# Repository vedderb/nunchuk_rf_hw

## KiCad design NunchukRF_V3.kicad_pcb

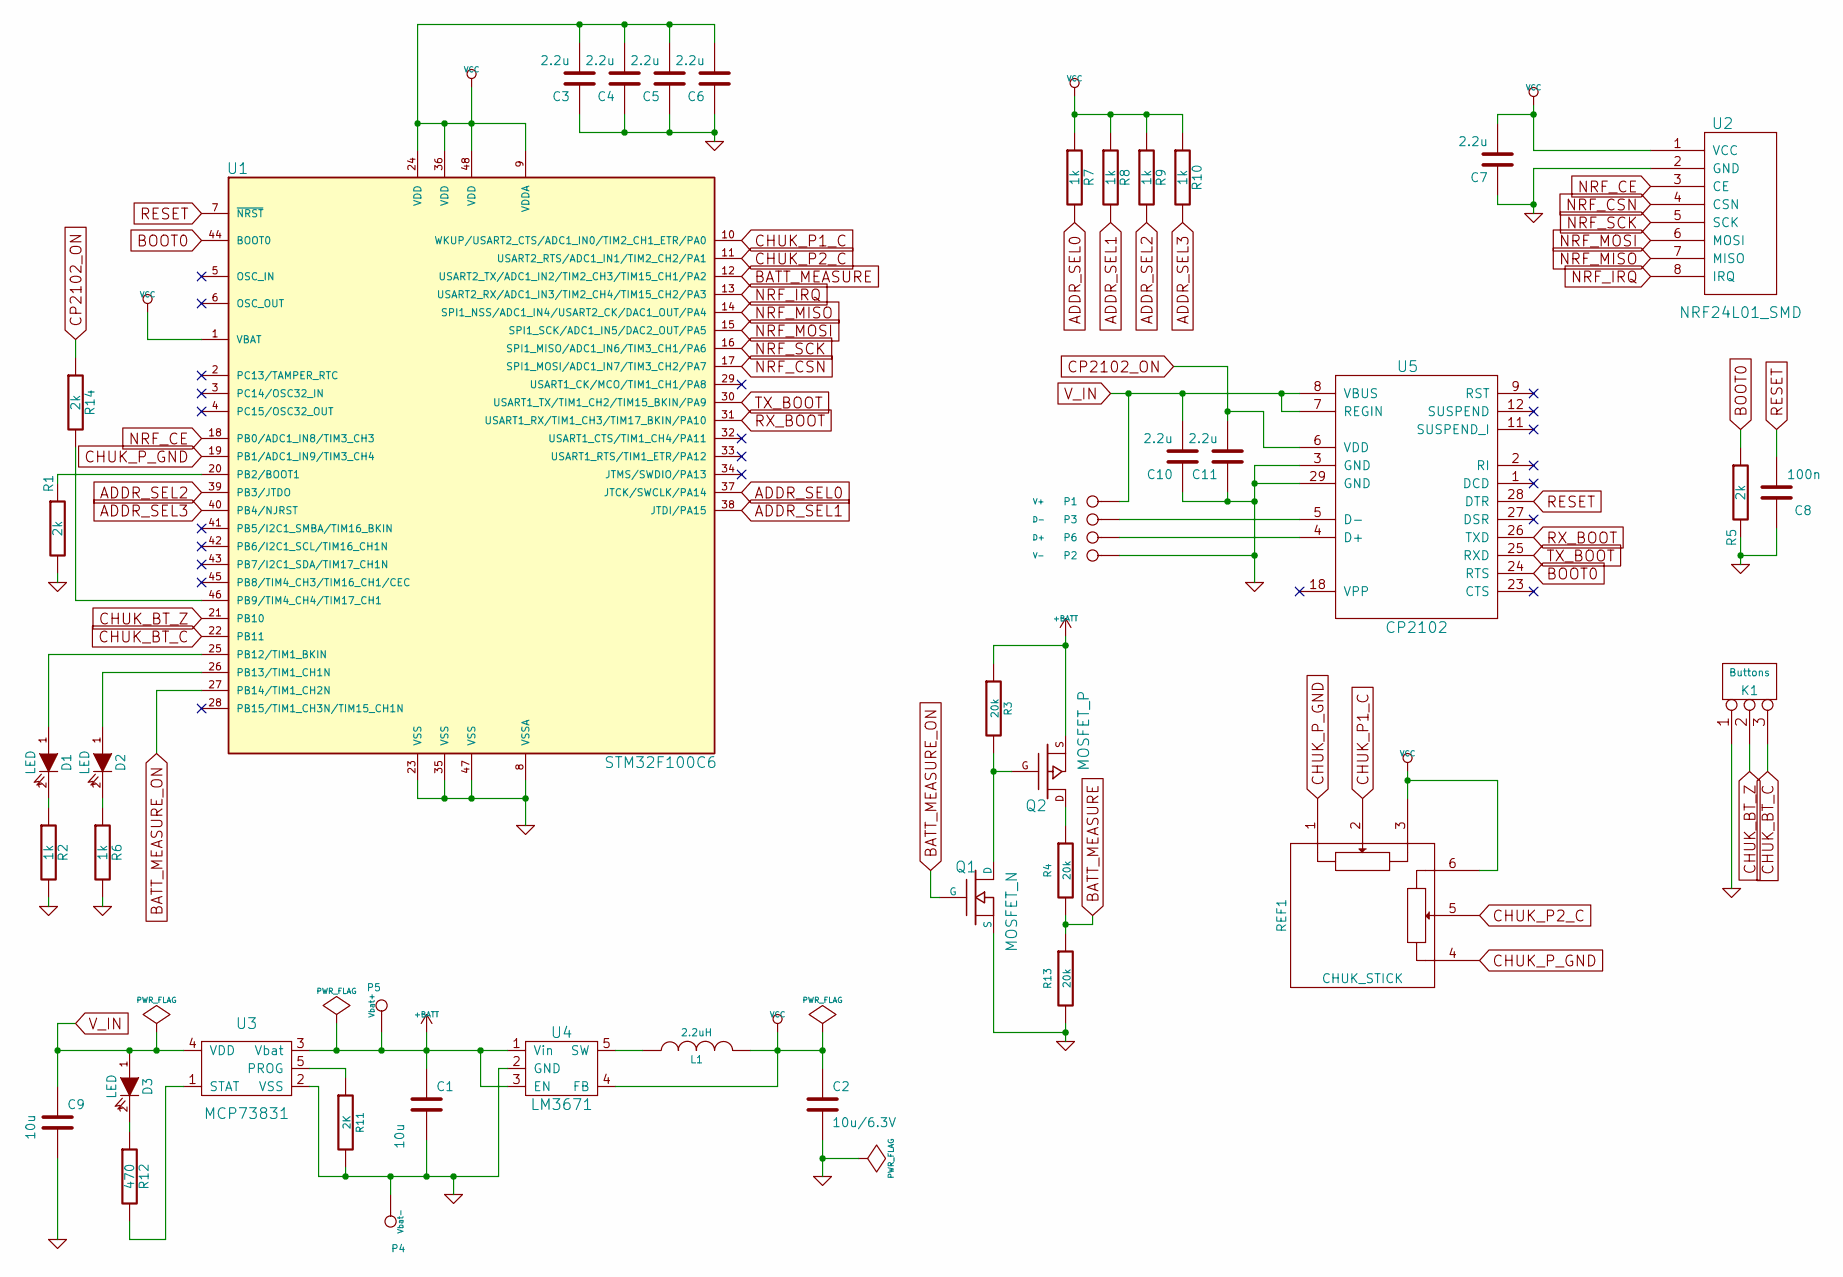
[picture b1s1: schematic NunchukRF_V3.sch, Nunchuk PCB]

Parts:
C1, C9: 10u; C_0603_HandSoldering
C2: 10u/6.3V; C_0603_HandSoldering
C3, C4, C5, C6, C7, C10, C11: 2.2u; C_0603_HandSoldering
C8: 100n; C_0603_HandSoldering
D1, D2, D3: LED; LED-0805
K1: Buttons; Wafer_Vertical10x5.8x7RM2.5-3
L1: 2.2uH; R_0805_HandSoldering
P1: V+; 1PAD_Small
P2: V-; 1PAD_Small
P3: D-; 1PAD_Small
P4: Vbat-; 1PAD_Small
P5: Vbat+; 1PAD_Small
P6: D+; 1PAD_Small
Q1: MOSFET_N; SOT23GDS
Q2: MOSFET_P; SOT23GDS
R1, R5, R14: 2k; R_0603_HandSoldering
R2, R6, R7, R8, R9, R10: 1k; R_0603_HandSoldering
R3, R4, R13: 20k; R_0603_HandSoldering
R11: 2K; R_0603_HandSoldering
R12: 470; R_0603_HandSoldering
REF1: CHUK_STICK; chuk_stick_2
U1: STM32F100C6; lqfp48_pad_mod
U2: NRF24L01_SMD
U3: MCP73831; SOT23-5
U4: LM3671; SOT23-5
U5: CP2102; qfn-28

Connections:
+BATT: C1.1, P5.1, Q2.S, R3.1, U3.3 (Vbat), U4.1 (Vin), U4.3 (EN)
ADDR_SEL0: R7.2, U1.37 (JTCK/SWCLK/PA14)
ADDR_SEL1: R8.2, U1.38 (JTDI/PA15)
ADDR_SEL2: R9.2, U1.39 (PB3/JTDO)
ADDR_SEL3: R10.2, U1.40 (PB4/NJRST)
BATT_MEASURE: R4.2, R13.1, U1.12 (USART2_TX/ADC1_IN2/TIM2_CH3/TIM15_CH1/P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)
BATT_MEASURE_ON: Q1.G, U1.27 (PB14/TIM1_CH2N)
BOOT0: R5.1, U1.44 (BOOT0), U5.24 (RTS)
CHUK_BT_C: K1.3, U1.22 (PB11)
CHUK_BT_Z: K1.2 (PM), U1.21 (PB10)
CHUK_P1_C: REF1.2 (P1_B), U1.10 (WKUP/USART2_CTS/ADC1_IN0/TIM2_CH1_ETR/P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)
CHUK_P2_C: REF1.5 (P2_B), U1.11 (USART2_RTS/ADC1_IN1/TIM2_CH2/PA1)
CHUK_P_GND: REF1.1 (P1_A), REF1.4 (P2_A), U1.19 (PB1/ADC1_IN9/TIM3_CH4)
CP2102_ON: C11.2, R14.1, U5.6 (VDD)
GND: C1.2, C2.2, C3.1, C4.1, C5.1, C6.1, C7.1, C8.1, C9.2, C10.1, C11.1, K1.1, P2.1, P4.1, Q1.S, R1.2, R2.2, R5.2, R6.2, R11.2, R13.2, U1.8 (VSSA), U1.23 (VSS), U1.35 (VSS), U1.47 (VSS), U2.2 (GND), U3.2 (VSS), U4.2 (GND), U5.3 (GND), U5.29 (GND)
NRF_CE: U1.18 (PB0/ADC1_IN8/TIM3_CH3), U2.3 (CE)
NRF_CSN: U1.17 (SPI1_MOSI/ADC1_IN7/TIM3_CH2/PA7), U2.4 (CSN)
NRF_IRQ: U1.13 (USART2_RX/ADC1_IN3/TIM2_CH4/TIM15_CH2/P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), U2.8 (IRQ)
NRF_MISO: U1.14 (SPI1_NSS/ADC1_IN4/USART2_CK/DAC1_OUT/PA4), U2.7 (MISO)
NRF_MOSI: U1.15 (SPI1_SCK/ADC1_IN5/DAC2_OUT/PA5), U2.6 (MOSI)
NRF_SCK: U1.16 (SPI1_MISO/ADC1_IN6/TIM3_CH1/PA6), U2.5 (SCK)
unnamed: D1.1 (A), U1.25 (PB12/TIM1_BKIN)
unnamed: D1.2 (K), R2.1
unnamed: D2.1 (A), U1.26 (PB13/TIM1_CH1N)
unnamed: D2.2 (K), R6.1
unnamed: D3.2 (K), R12.1
unnamed: L1.1, U4.5 (SW)
unnamed: P3.1, U5.5 (D-)
unnamed: P6.1, U5.4 (D+)
unnamed: Q1.D, Q2.G, R3.2
unnamed: Q2.D, R4.1
unnamed: R1.1, U1.20 (PB2/BOOT1)
unnamed: R11.1, U3.5 (PROG)
unnamed: R12.2, U3.1 (STAT)
unnamed: R14.2, U1.46 (PB9/TIM4_CH4/TIM17_CH1)
RESET: C8.2, U1.7 (~NRST), U5.28 (DTR)
RX_BOOT: U1.31 (USART1_RX/TIM1_CH3/TIM17_BKIN/PA10), U5.26 (TXD)
TX_BOOT: U1.30 (USART1_TX/TIM1_CH2/TIM15_BKIN/PA9), U5.25 (RXD)
VCC: C2.1, C3.2, C4.2, C5.2, C6.2, C7.2, L1.2, R7.1, R8.1, R9.1, R10.1, REF1.3 (P1_C), REF1.6 (P2_C), U1.1 (VBAT), U1.9 (VDDA), U1.24 (VDD), U1.36 (VDD), U1.48 (VDD), U2.1 (VCC), U4.4 (FB)
V_IN: C9.1, C10.2, D3.1 (A), P1.1, U3.4 (VDD), U5.7 (REGIN), U5.8 (VBUS)

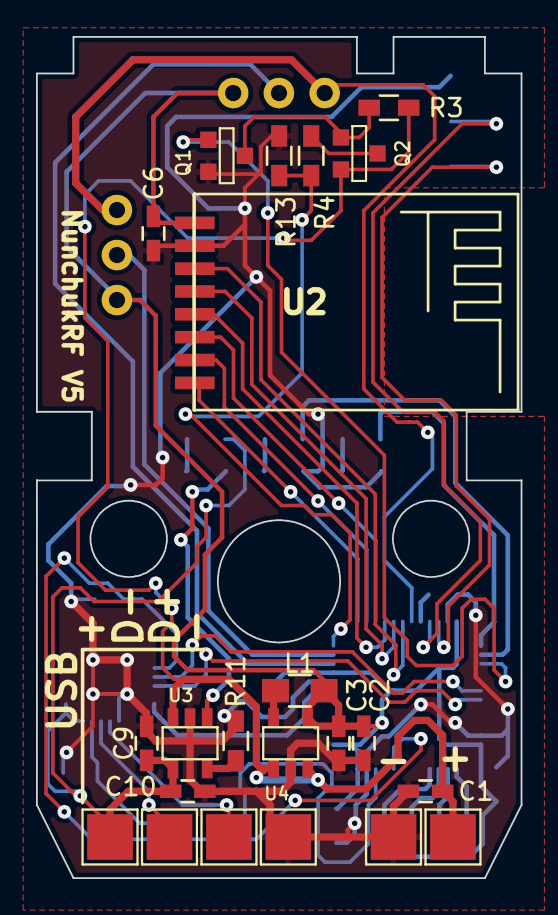
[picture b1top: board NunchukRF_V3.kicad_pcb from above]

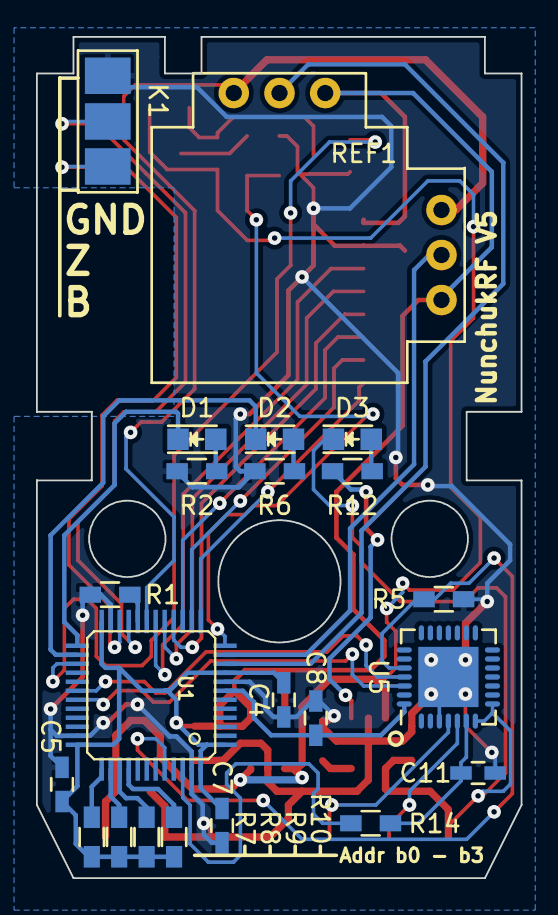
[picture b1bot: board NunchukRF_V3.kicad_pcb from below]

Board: 2 copper layers, 26.9 x 46.7 mm, 44 parts (22 on the bottom side), 40 nets.

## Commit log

2015-08-19 Added cp2102 power detect connection to mcu
2015-08-20 Updated NRF labels
2015-08-20 Updated BOM
2015-08-23 Updated 3d pictures and saved using the latest kicad version
2015-08-31 Changed CP2102 footprint
2015-09-17 Small update
2015-10-19 Moved nrf, changed button connector, updated labels
